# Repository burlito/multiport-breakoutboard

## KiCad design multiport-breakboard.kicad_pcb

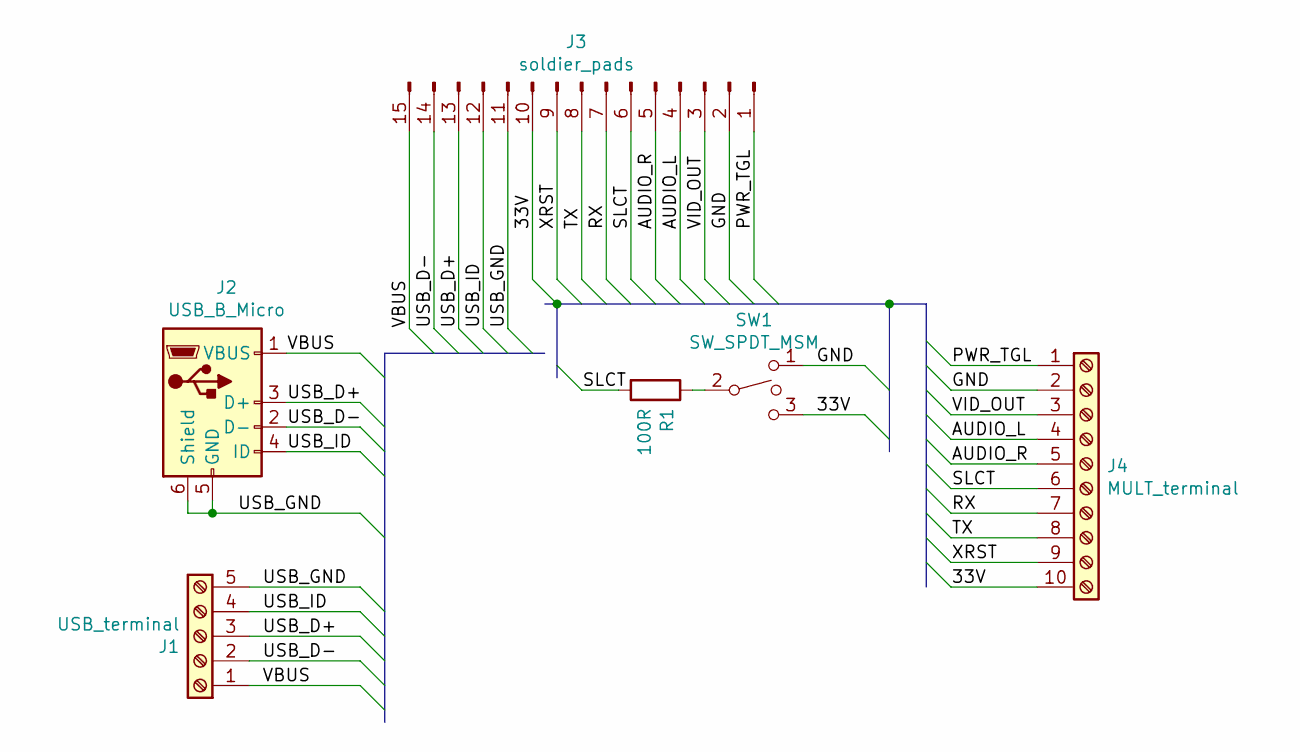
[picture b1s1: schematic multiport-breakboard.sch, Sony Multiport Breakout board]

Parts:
J1: USB_terminal; TerminalBlock_Phoenix_MKDS-1,5-5-5.08_1x05_P5.08mm_Horizont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
J2: USB_B_Micro; USB_Micro-B_Molex_47346-0001
J3: soldier_pads; DSUB-15_Female_Horizontal_P2.77x2.84mm_EdgePinOffset9.40mm
J4: MULT_terminal; TerminalBlock_Phoenix_MKDS-1,5-10-5.08_1x10_P5.08mm_Horizon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
R1: 100R; R_Axial_DIN0411_L9.9mm_D3.6mm_P15.24mm_Horizontal
SW1: SW_SPDT_MSM; SW_E-Switch_EG1224_SPDT_Angled

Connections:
/33V: J3.10, J4.10, SW1.3
/AUDIO_L: J3.4, J4.4
/AUDIO_R: J3.5, J4.5
/GND: J3.2, J4.2, SW1.1
/PWR_TGL: J3.1, J4.1
/RX: J3.7, J4.7
/SLCT: J3.6, J4.6, R1.2
/TX: J3.8, J4.8
/USB_D+: J1.3, J2.3 (D+), J3.13
/USB_D-: J1.2, J2.2 (D-), J3.14
/USB_GND: J1.5, J2.5 (GND), J2.6 (Shield), J3.11
/USB_ID: J1.4, J2.4 (ID), J3.12
/VBUS: J1.1, J2.1 (VBUS), J3.15
/VID_OUT: J3.3, J4.3
/XRST: J3.9, J4.9
unnamed: R1.1, SW1.2

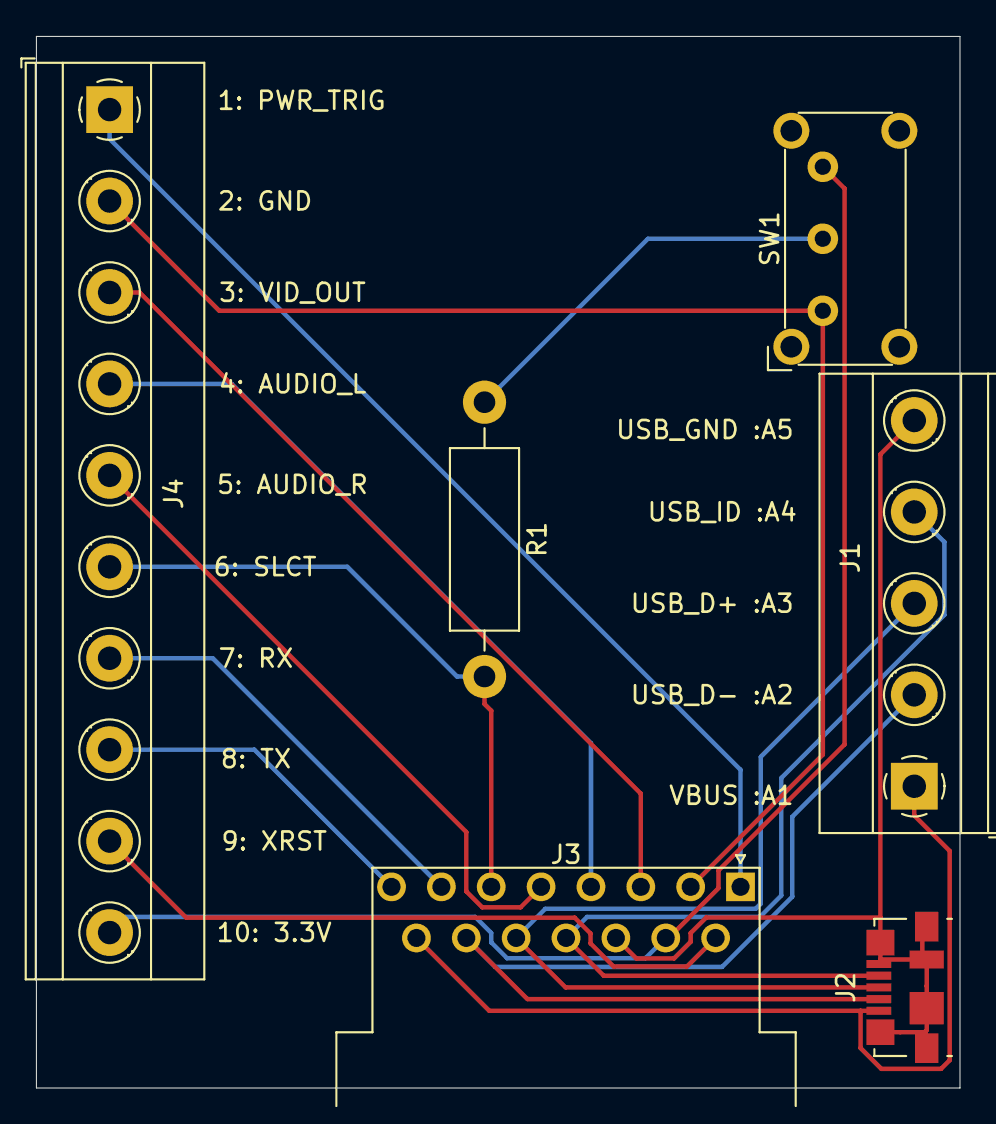
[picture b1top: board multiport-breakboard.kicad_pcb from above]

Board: 2 copper layers, 51.3 x 58.4 mm, 6 parts (0 on the bottom side), 16 nets.

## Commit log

2020-05-22 Initial design of board
2020-05-22 Assigned footprints
2020-05-22 Revision 0.1
    Revision just before submiting to david
